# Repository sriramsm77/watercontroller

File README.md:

# watercontroller
Code for water level controller based on Raspberry Pi

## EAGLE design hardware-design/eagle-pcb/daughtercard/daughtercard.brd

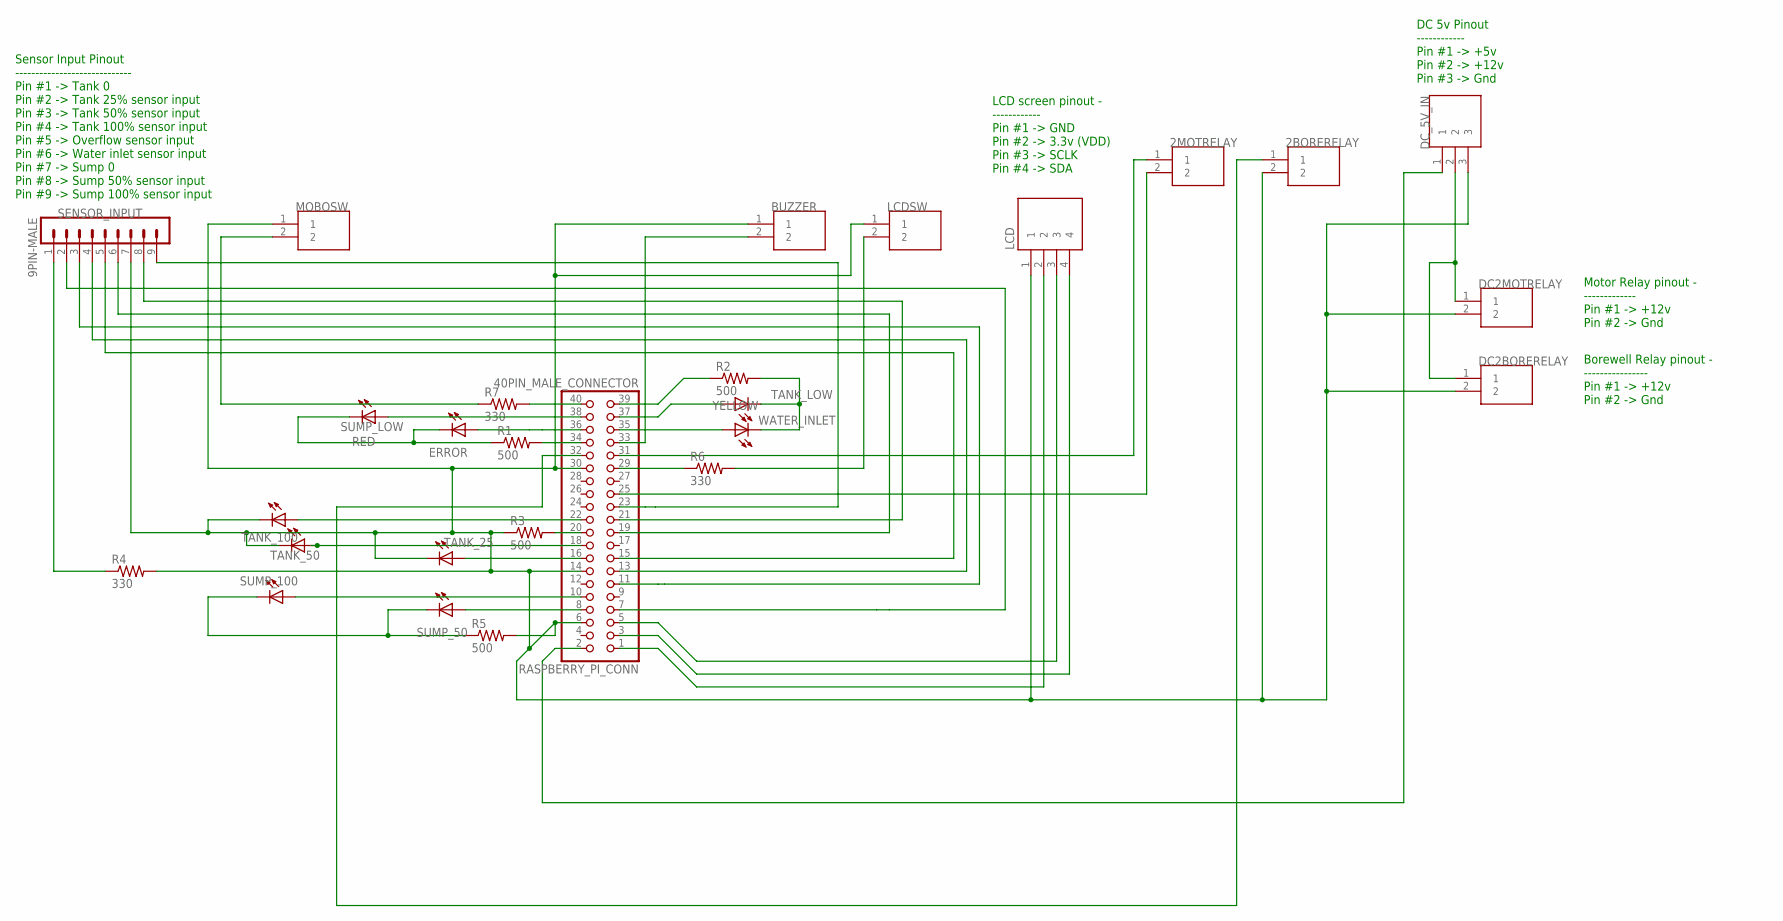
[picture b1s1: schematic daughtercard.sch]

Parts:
2BORERELAY, 2MOTRELAY: 440055-2; TE_440055-2
BUZZER: 440055-2; TE_440055-2
DC2BORERELAY, DC2MOTRELAY: 440055-2; TE_440055-2
DC_5V_IN: 440052-3; TE_440052-3
ERROR: RED; LED3MM
LCD: 110990030; SEEED_110990030
LCDSW: 440055-2; TE_440055-2
MOBOSW: 440055-2; TE_440055-2
R1, R2, R5: 500; 0204V
R3: 500; 0204/7
R4: 330; 0204/7
R6, R7: 330; 0204V
RASPBERRY_PI_CONN: 40PIN_MALE_CONNECTOR; 2X20
SENSOR_INPUT: 9PIN-MALE; MA09-1
SUMP_50, SUMP_100: GREEN; LED3MM
SUMP_LOW: RED; LED3MM
TANK_25, TANK_50, TANK_100: GREEN; LED3MM
TANK_LOW: RED; LED3MM
WATER_INLET: YELLOW; LED3MM

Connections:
unnamed: RASPBERRY_PI_CONN.19, SENSOR_INPUT.6
unnamed: 2MOTRELAY.1, RASPBERRY_PI_CONN.31
unnamed: DC2BORERELAY.1, DC2MOTRELAY.1, DC_5V_IN.2
unnamed: 2BORERELAY.2, BUZZER.1, DC2BORERELAY.2, DC2MOTRELAY.2, DC_5V_IN.3, LCD.1, LCDSW.1, MOBOSW.1, R3.1, R4.2, R5.2, RASPBERRY_PI_CONN.6, RASPBERRY_PI_CONN.14, RASPBERRY_PI_CONN.30, SENSOR_INPUT.7, TANK_25.K (C), TANK_50.K (C), TANK_100.K (C)
unnamed: R1.2, RASPBERRY_PI_CONN.34
unnamed: RASPBERRY_PI_CONN.21, SENSOR_INPUT.8
unnamed: R3.2, RASPBERRY_PI_CONN.20
unnamed: R4.1, SENSOR_INPUT.1
unnamed: RASPBERRY_PI_CONN.23, SENSOR_INPUT.9
unnamed: 2BORERELAY.1, RASPBERRY_PI_CONN.32
unnamed: LCD.4, RASPBERRY_PI_CONN.3
unnamed: LCD.3, RASPBERRY_PI_CONN.5
unnamed: RASPBERRY_PI_CONN.18, TANK_50.A
unnamed: R5.1, SUMP_50.K (C), SUMP_100.K (C)
unnamed: R2.1, RASPBERRY_PI_CONN.39
unnamed: LCDSW.2, R6.2
unnamed: R6.1, RASPBERRY_PI_CONN.29
unnamed: R7.2, RASPBERRY_PI_CONN.40
unnamed: 2MOTRELAY.2, RASPBERRY_PI_CONN.25
unnamed: RASPBERRY_PI_CONN.15, SENSOR_INPUT.5
unnamed: ERROR.K (C), R1.1, SUMP_LOW.K (C)
unnamed: R2.2, TANK_LOW.K (C), WATER_INLET.K (C)
unnamed: ERROR.A, RASPBERRY_PI_CONN.36
unnamed: RASPBERRY_PI_CONN.38, SUMP_LOW.A
unnamed: RASPBERRY_PI_CONN.22, TANK_100.A
unnamed: MOBOSW.2, R7.1
unnamed: RASPBERRY_PI_CONN.16, TANK_25.A
unnamed: RASPBERRY_PI_CONN.10, SUMP_100.A
unnamed: RASPBERRY_PI_CONN.37, TANK_LOW.A
unnamed: RASPBERRY_PI_CONN.8, SUMP_50.A
unnamed: RASPBERRY_PI_CONN.35, WATER_INLET.A
unnamed: RASPBERRY_PI_CONN.7, SENSOR_INPUT.2
unnamed: RASPBERRY_PI_CONN.11, SENSOR_INPUT.3
unnamed: RASPBERRY_PI_CONN.13, SENSOR_INPUT.4
unnamed: BUZZER.2, RASPBERRY_PI_CONN.33
VDD: LCD.2, RASPBERRY_PI_CONN.1
VO: DC_5V_IN.1, RASPBERRY_PI_CONN.2

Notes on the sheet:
Sensor Input Pinout ----------------------------- Pin #1 -> Tank 0 Pin #2 -> Tank 25% sensor input Pin #3 -> Tank 50% sensor input Pin #4 -> Tank 100% sensor input Pin #5 -> Overflow sensor input Pin #6 -> Water inlet sensor input Pin #7 -> Sump 0 Pin #8 -> Sump 50% sensor input Pin #9 -> Sump 100%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
LCD screen pinout - ------------ Pin #1 -> GND Pin #2 -> 3.3v (VDD) Pin #3 -> SCLK Pin #4 -> SDA
DC 5v Pinout ------------ Pin #1 -> +5v Pin #2 -> +12v Pin #3 -> Gnd
Motor Relay pinout - ------------- Pin #1 -> +12v Pin #2 -> Gnd
Borewell Relay pinout - ---------------- Pin #1 -> +12v Pin #2 -> Gnd

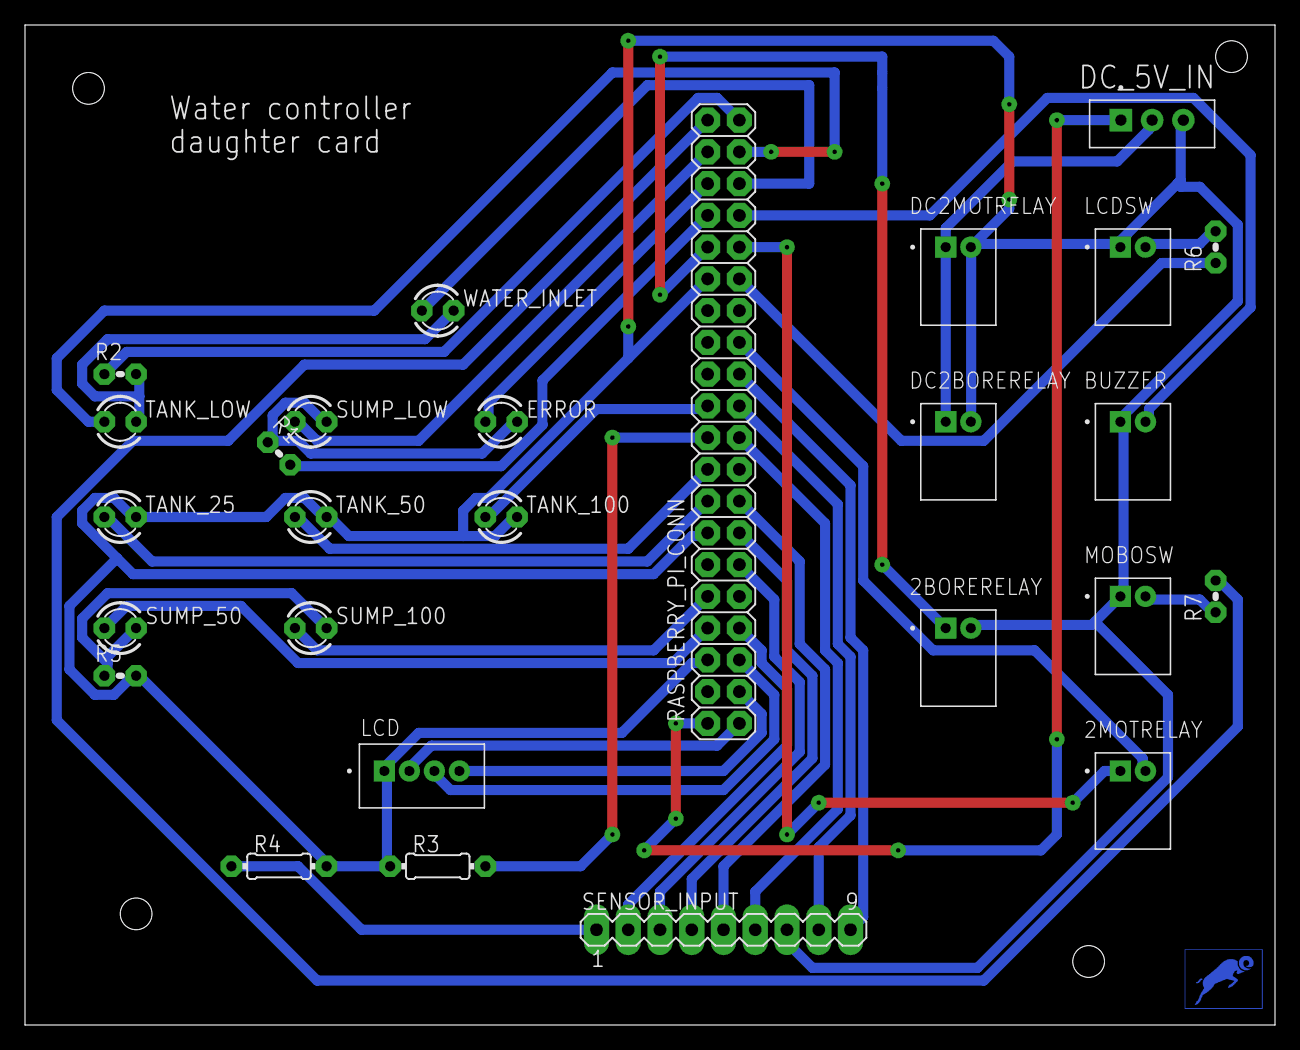
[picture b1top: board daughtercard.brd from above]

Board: 2 copper layers, 100.0 x 80.0 mm, 27 parts (0 on the bottom side), 37 nets.

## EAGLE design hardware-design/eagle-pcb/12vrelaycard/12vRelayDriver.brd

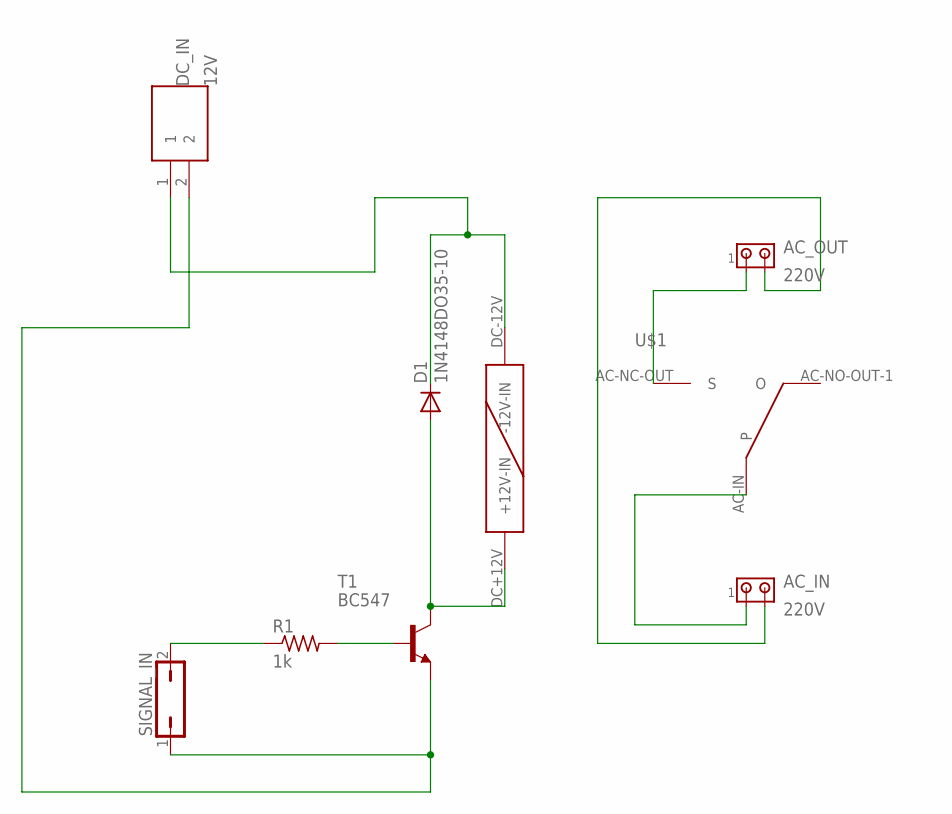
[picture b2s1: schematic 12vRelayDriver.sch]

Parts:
AC_IN: 220V; 1X2MTA
AC_OUT: 220V; 1X2MTA
D1: 1N4148DO35-10; DO35-10
DC_IN: 12V; TE_440055-2
R1: 1k; 0204/7
SIGNAL_IN: JP1Q; JP1
T1: BC547; TO92
U$1: GU-D-2-6

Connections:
unnamed: D1.A, T1.3 (C), U$1.DC+12V (+12V-IN)
unnamed: AC_OUT.1, U$1.AC-NC-OUT (S)
unnamed: AC_IN.2, AC_OUT.2
unnamed: R1.2, T1.2 (B)
unnamed: R1.1, SIGNAL_IN.2
unnamed: AC_IN.1, U$1.AC-IN
unnamed: D1.C, DC_IN.1, U$1.DC-12V (-12V-IN)
unnamed: DC_IN.2, SIGNAL_IN.1, T1.1 (E)

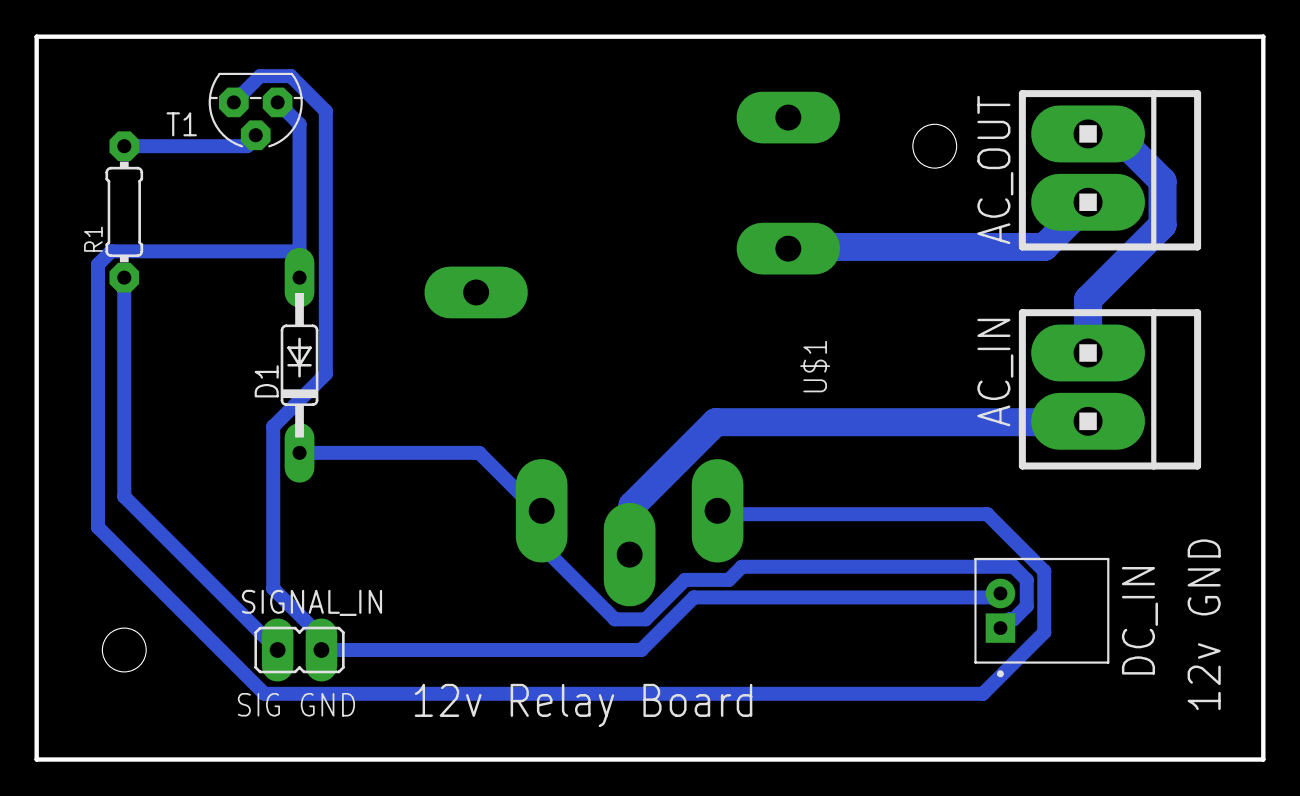
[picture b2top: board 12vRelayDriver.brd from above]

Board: 2 copper layers, 71.1 x 41.9 mm, 8 parts (0 on the bottom side), 8 nets.

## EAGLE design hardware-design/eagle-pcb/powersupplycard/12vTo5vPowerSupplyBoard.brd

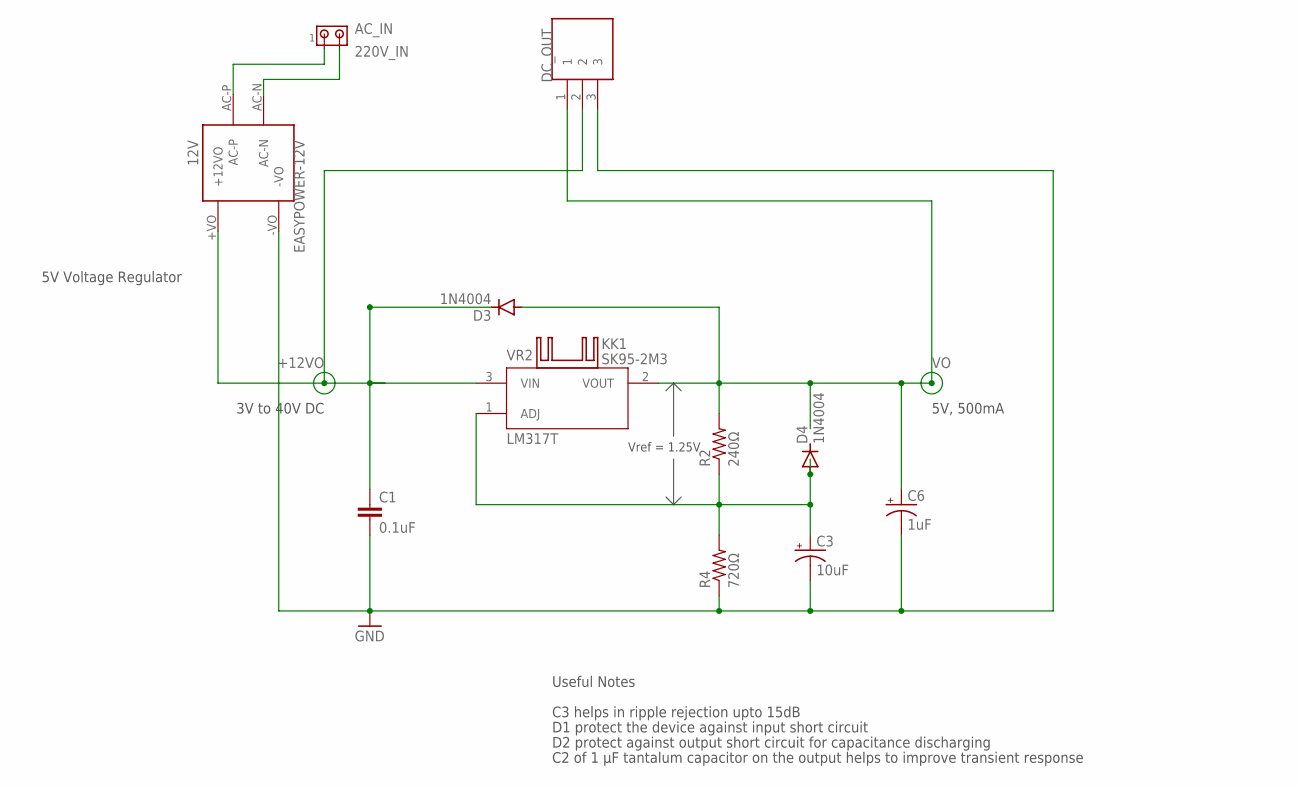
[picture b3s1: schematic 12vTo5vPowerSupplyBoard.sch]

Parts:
AC_IN: 220V_IN; 1X2MTA
C1: 0.1uF; C2.5-2
C3: 10uF; E2,5-5
C6: 1uF; E2,5-5
D3, D4: 1N4004; DO41-10
DC_OUT: 440052-3; TE_440052-3
EASYPOWER-12V: 12V; SO12V200
KK1: SK95-2M3
R2: 240Ω; 0204V
R4: 720Ω; 0204V
VR2: LM317T; TO254P1054X470X1955-3

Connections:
+12VO: C1.1, D3.C, DC_OUT.2, EASYPOWER-12V.+VO (+12VO), VR2.3 (VIN)
GND: C1.2, C3.-, C6.-, DC_OUT.3, EASYPOWER-12V.-VO, R4.1
unnamed: AC_IN.1, EASYPOWER-12V.AC-P
unnamed: AC_IN.2, EASYPOWER-12V.AC-N
unnamed: C3.+, D4.A, R2.1, R4.2, VR2.1 (ADJ)
VO: C6.+, D3.A, DC_OUT.1, R2.2, VR2.2 (VOUT)

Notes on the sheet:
5V Voltage Regulator
C3 helps in ripple rejection upto 15dB
D1 protect the device against input short circuit
D2 protect against output short circuit for capacitance discharging
C2 of 1 µF tantalum capacitor on the output helps to improve transient response
Useful Notes
5V, 500mA
3V to 40V DC
Vref = 1.25V

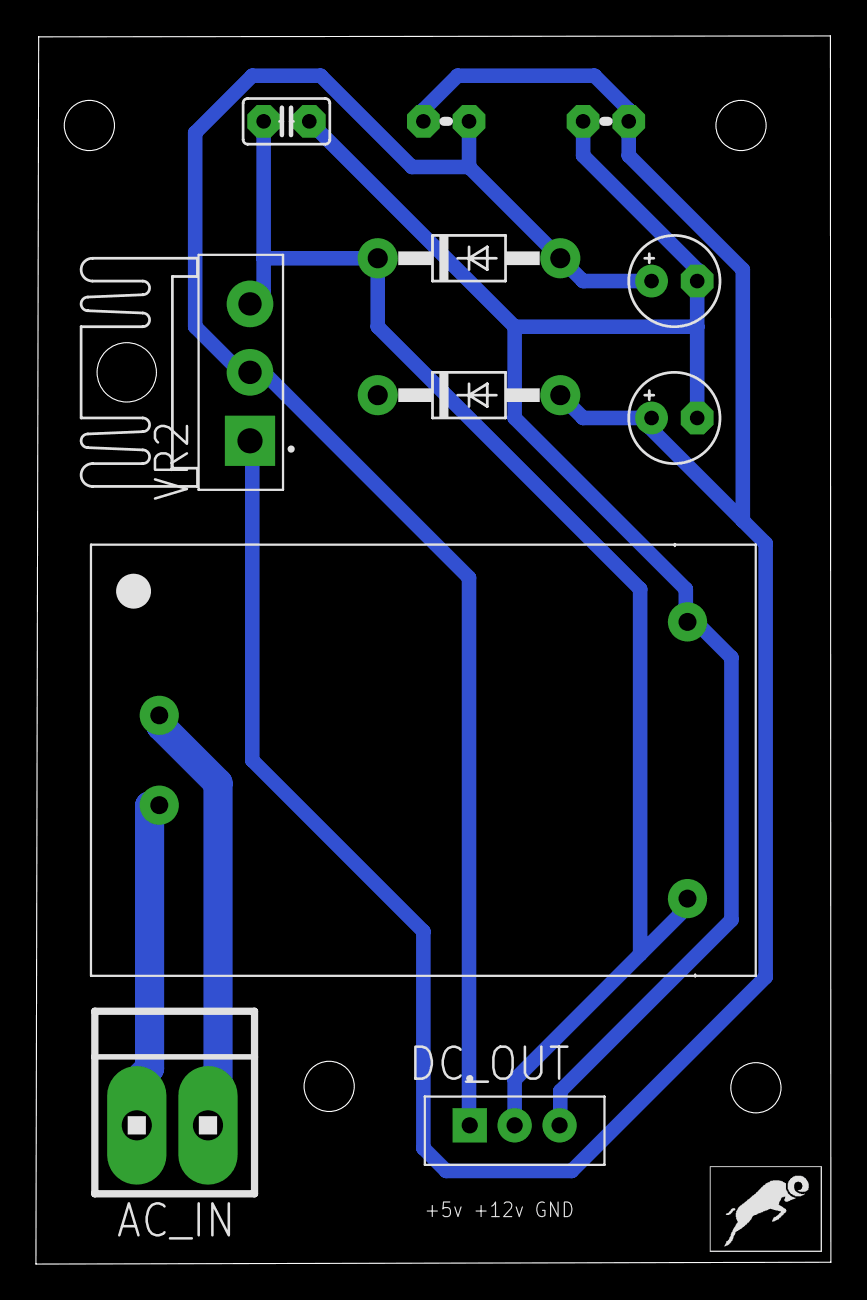
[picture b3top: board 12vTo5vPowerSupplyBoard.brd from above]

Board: 2 copper layers, 44.2 x 68.4 mm, 12 parts (0 on the bottom side), 6 nets.

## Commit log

2023-03-23 Incorporated hardware design
